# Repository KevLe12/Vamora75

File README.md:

# Vamora75

**An 82-key 75 % mechanical keyboard with a 6° typing angle, a tab-gasket mount, hot-swap sockets
and an on-board RP2040.** Designed by **Kevin Le, Sammy DeGraaff and Mohammed-Mehdi Hamdaoui**.

> **Status: revision 1.7, prototype design checked in software, not built yet.** ERC, DRC, schematic
> parity, plate DRC, CAD interference checks and 34 firmware tests all pass
> ([validation/STATUS.md](validation/STATUS.md)). Build one prototype before a group order and work
> through the open items in [DESIGN_REVIEW.md](DESIGN_REVIEW.md).

Revision 1.4 adopts all 82 key positions and widths from the supplied Custom layout,
including the closer F-row, inward navigation column and End in the top row.
Revision 1.5 moves the controller beside the rear-left USB-C connector and uses four layers.
The short USB pair targets 90 ohms on JLCPCB's JLC04161H-7628 stackup, with a dedicated
In2.Cu ground plane. Order controlled impedance and request the supplier's coupon report;
see [fabrication notes](Manufacturing/FABRICATION.md). Key positions and case geometry are unchanged.

Revision 1.6 incorporates the friend/professor review: USB enters the ESD device on
pins 1/3 and exits on pins 6/4, without PCB copper bypasses. C8 adds a correctly
specified 100 nF 0402 VBUS bypass capacitor. USB track junctions now meet on their
centrelines or at pad/via centres, and termination via drills clear the resistor pads.
The PCB order specifies **black solder mask**, white silkscreen and ENIG.
See [feedback resolution](validation/FEEDBACK_RESOLUTION.md).

Revision 1.7 centres the remaining trace-to-via connections and enables that DRC check.
It adds component-to-component CAD checks, fixes the QMK metadata and protects
CircuitPython boot recovery when the USB host is suspended. See
[release audit](validation/RELEASE_AUDIT.md). In KiCad 3D Viewer, enable
**Appearance → Use board stackup colors** and refresh to display the black mask.

CNC case revision **D5** uses blind M3 threads and 3 mm BOOT access. Send the
[CNC package](Manufacturing/Case_Drawings/Vamora75_case_CNC_D5_package.zip), including its drawings,
to the machinist. It specifies 6061-T6, as machined and deburred; preview colors are illustrative.
Separate print variants retain heat-set inserts. Validate one machined pair before repeating it.

For **PC-CF on the CORE One L**, use the [print package](Manufacturing/Vamora75_PCCF_print.zip)
and [PC-CF guide](Manufacturing/PCCF_PRINT.md). Four oriented parts fit the bed individually;
the package includes an insert-fit coupon. Material budget: three 800 g spools for three cases,
pending actual slicing and first-case validation.

## Features

- Compact 75 % Windows ANSI layout, 82 keys, matching the full Custom layout
- Hot-swap Kailh sockets for any 3- or 5-pin MX-compatible switch
- PCB-mount screw-in stabilisers on plated, copper-reinforced holes; the plate openings let the
  stabiliser housings pass through
- Tab-gasket sandwich mount: 8 plate tabs, 16 gaskets at 20 % compression, optional flex-cut plate
- 6° typing angle; two-piece case whose top follows the key clusters, so no plate shows between
  them; printed in one piece, in 4 pieces for 250 x 210 mm beds, or CNC
- RP2040 on the board (the Raspberry Pi Pico core circuit), USB-C, ESD protection, fuse, BOOT and
  RESET buttons
- QMK + VIA, or CircuitPython with no compiler
- Black PCB with ENIG gold; "Vamora75" across the PCB front, engraved under the case and in gold on
  the plate (under the top case); *Nam Quốc Sơn Hà* and the designers' names on the PCB back
- Generated from source: one command rebuilds the PCB, plate, case, firmware, manufacturing files,
  3D models and renders, then re-runs every check

## Gallery

| Exploded | Top |
|---|---|
|  |  |
| **Profile** | **Underside** |
|  |  |

**PCB + plate + components** (no case): Joe Scotto's MX switches, the PCB-mount stabilisers, Kailh
sockets and every SMD part ([3D file](Mechanical/Vamora75_PCB_plate.step),
[quick-look .glb](Mechanical/Vamora75_PCB_plate.glb)):

### PCB

| Front ("Vamora75" silkscreen) | Back (*Nam Quốc Sơn Hà*, designers, gold stabiliser rings) |
|---|---|
|  |  |
| **With Joe Scotto's switch models** | **FR4 plate (name in gold ENIG, under the top case)** |
|  |  |

## 3D files

| File | Shows | Open with |
|---|---|---|
| [Mechanical/Vamora75_assembly.step](Mechanical/Vamora75_assembly.step) | The whole keyboard: case, gaskets, foams, plate, PCBA, switches, stabilisers, keycaps | FreeCAD, Fusion 360, Onshape, SolidWorks |
| [Mechanical/Vamora75_PCB_plate.step](Mechanical/Vamora75_PCB_plate.step) | PCB + plate + every component, without the case | any STEP viewer |
| [Mechanical/Vamora75_PCB_plate.glb](Mechanical/Vamora75_PCB_plate.glb) | The same, as a light coloured model | Windows 3D Viewer, Blender, any web glTF viewer |
| [Mechanical/Vamora75_PCBA.step](Mechanical/Vamora75_PCBA.step) | The PCBA only (KiCad export) | any STEP viewer |
| [PCB/Vamora75.kicad_pro](PCB/Vamora75.kicad_pro) | Schematic and board; press Alt+3 for the 3D view | KiCad 10 |

Case parts, the plate and the soft parts are in [Mechanical/](Mechanical) as STEP/STL/DXF.

## Specifications

| | |
|---|---|
| Layout | 82 keys: exploded 75 % Windows ANSI with an F-row in clusters, a Del/Home/PgUp/PgDn/End column, Custom-style arrow positions (0.25u gaps to RShift and RCtrl; 0.25u lower), 1.75u RShift and 6.25u space ([layout](Previews/layout.png)) |
| Switches | Any MX-compatible switch, 3- or 5-pin, in Kailh CPG151101S11 hot-swap sockets (ScottoKicad `Hotswap_MX` footprints) |
| Stabilisers | PCB-mount screw-in: Backspace (2u), Enter and LShift (2.25u), Space (6.25u), standard orientation. Plated holes with 4.6 / 6.0 mm copper reinforcement rings; plate openings 7.0 x 14 mm |
| Controller | RP2040, W25Q16JV 2 MB flash, 12 MHz crystal (the Raspberry Pi Pico core circuit), BOOT and RESET buttons |
| USB | USB-C (HRO TYPE-C-31-M-12), USB 2.0 full speed, 5.1 kΩ CC resistors (C-C and A-C cables), USBLC6-2SC6 ESD protection, 0.5 A PTC fuse, XC6206 3.3 V LDO |
| Matrix | 6 x 16, COL2ROW, one 1N4148W per key |
| PCB | 315.56 x 129.83 mm, 4 layers, 1.6 mm nominal, black solder mask, white silkscreen, ENIG. All SMT parts on the bottom (one-sided assembly), dedicated In2.Cu GND plane plus outer ground pours |
| Plate | FR4, 1.5 mm (1.6 mm also fits), black, 8 gasket tabs, optional flex cuts, "Vamora75" in gold ENIG |
| Mount | Tab-gasket sandwich: 16 gaskets of 20 x 4.5 x 2 mm at 20 % compression. PCB and plate float as one unit |
| Case | Two pieces, 6° typing angle, 20.98 mm high at the front and 37.06 mm at the rear, 339.56 x 156.73 mm. CNC D5: 8 M3 screws into blind M3 x 0.5 threads. Separate print variants use heat-set inserts. "Vamora75" engraved underneath |
| Firmware | QMK + VIA, or CircuitPython |

## Bill of materials

<!-- BOM:start (generated by Source/export_manufacturing.py) -->
Full list: [BOM.csv](BOM.csv). The PCBA parts are placed by JLCPCB from
[Vamora75_BOM_JLCPCB.csv](Manufacturing/PCB/Vamora75_BOM_JLCPCB.csv) and
[Vamora75_CPL_JLCPCB.csv](Manufacturing/PCB/Vamora75_CPL_JLCPCB.csv); you only buy the kit items.

**Kit: what to buy or make**

| Item | Qty | Specification | Source / file |
|---|---|---|---|
| PCBA (this design) | 1 | 4-layer JLC04161H-7628 1.6 mm nominal, black mask, ENIG, bottom SMT, USB 90 ohm +/-10% | Manufacturing/PCB - JLCPCB |
| FR4 plate | 1 | 1.5 mm (1.6 mm fits), black mask, ENIG for the gold name | Manufacturing/Plate - any PCB fab |
| Case top | 1 | CNC D5 6061-T6; separate PETG/ASA print variant | Mechanical/Case (CNC); print_one_piece or print_split (print) |
| Case bottom | 1 | CNC D5 6061-T6 solid wedge, 6 deg; separate print variant | Mechanical/Case (CNC); print_one_piece or print_split (print) |
| MX-compatible switches | 82 | 3-pin or 5-pin | user choice |
| Keycaps | 82 | 1u x 71, 1.25u x 3, 1.5u x 2, 1.75u x 2, 2u x 1, 2.25u x 2, 6.25u x 1 | any MX set with a 75 % kit (1.75u RShift, 6.25u space) |
| PCB-mount screw-in stabilisers | 4 | 3 x 2u (Backspace, Enter, LShift) + 1 x 6.25u (Space) | Durock/Cherry/TX |
| Gaskets | 16 | 20 x 4.5 x 2 mm Poron 4701-50 or 40A silicone | Mechanical/Soft DXF |
| Case foam | 1 | 3 mm PE / Poron | Mechanical/Soft DXF |
| Plate foam (optional) | 1 | 3.5 mm Poron / PE, with stabiliser/wire windows | Mechanical/Soft DXF |
| Screws | 8 | M3 x 8 ISO 4762 socket head |  |
| Heat-set inserts (print only) | 8 | M3 x 4 x 4.0 mm heat-set insert (not used in CNC case) | Mechanical/Case/print_one_piece or print_split |
| Dowel pins (split print only) | 5 | 3 x 12 mm steel dowel (or printed pin) | only for the 4-piece printed case |
| Bumpers | 4 | 10 x 3 mm silicone bumper |  |
| USB-C cable | 1 | overmould <= 12.3 x 6.5 mm |  |

**PCBA: parts on the board** (198 placements, all on the bottom side)

| Part | Qty | Designators | Footprint | LCSC |
|---|---|---|---|---|
| 10uF CL10A106KP8NNNC | 2 | C1-C2 | C_0603_1608Metric | [C19702](https://www.lcsc.com/product-detail/C19702.html) |
| 100nF CL05B104KO5NNNC | 11 | C3-C12, C15 | Capacitor_0402 | [C1525](https://www.lcsc.com/product-detail/C1525.html) |
| 1uF CL05A105KA5NQNC | 2 | C13-C14 | Capacitor_0402 | [C52923](https://www.lcsc.com/product-detail/C52923.html) |
| 15pF 0402CG150J500NT | 2 | C16-C17 | Capacitor_0402 | [C1548](https://www.lcsc.com/product-detail/C1548.html) |
| 1N4148W | 82 | D1-D82 | Diode_SOD-123 | [C81598](https://www.lcsc.com/product-detail/C81598.html) |
| 500mA SMD0805-050 | 1 | F1 | Fuse_0805_2012Metric | [C66452](https://www.lcsc.com/product-detail/C66452.html) |
| HRO TYPE-C-31-M-12 | 1 | J1 | USB_C_HRO_TYPE-C-31-M-12 | [C165948](https://www.lcsc.com/product-detail/C165948.html) |
| 5.1k 0402WGF5101TCE | 2 | R1-R2 | Resistor_0402 | [C25905](https://www.lcsc.com/product-detail/C25905.html) |
| 27R 0402WGF270JTCE | 2 | R3-R4 | Resistor_0402 | [C25100](https://www.lcsc.com/product-detail/C25100.html) |
| 10k 0402WGF1002TCE | 2 | R5, R7 | Resistor_0402 | [C25744](https://www.lcsc.com/product-detail/C25744.html) |
| 1k 0402WGF1001TCE | 2 | R6, R8 | Resistor_0402 | [C11702](https://www.lcsc.com/product-detail/C11702.html) |
| Kailh CPG151101S11 MX hot-swap socket | 82 | SW1-SW82 | Kailh_CPG151101S11 | [C5156480](https://www.lcsc.com/product-detail/C5156480.html) |
| BOOT TS-1187A-B-A-B | 1 | SW90 | SW_Push_1P1T_XKB_TS-1187A | [C318884](https://www.lcsc.com/product-detail/C318884.html) |
| RESET TS-1187A-B-A-B | 1 | SW91 | SW_Push_1P1T_XKB_TS-1187A | [C318884](https://www.lcsc.com/product-detail/C318884.html) |
| RP2040 | 1 | U1 | QFN-56-1EP_7x7mm_P0.4mm_EP3.2x3.2mm_ThermalVias | [C2040](https://www.lcsc.com/product-detail/C2040.html) |
| USBLC6-2SC6 | 1 | U2 | ESD_SOT-23-6 | [C7519](https://www.lcsc.com/product-detail/C7519.html) |
| XC6206P332MR | 1 | U3 | Voltage_SOT-23 | [C5446](https://www.lcsc.com/product-detail/C5446.html) |
| W25Q16JVUXIQ | 1 | U4 | Winbond_USON-8-1EP_3x2mm_P0.5mm_EP0.2x1.6mm | [C2843335](https://www.lcsc.com/product-detail/C2843335.html) |
| 12MHz ABM8-272-T3 | 1 | Y1 | Crystal_SMD_3225-4Pin_3.2x2.5mm | [C20625731](https://www.lcsc.com/product-detail/C20625731.html) |
<!-- BOM:end -->

## Getting started

1. Read [DESIGN_REVIEW.md](DESIGN_REVIEW.md): the mount, the stabilisers, what changed, and what to
   check on the first prototype.
2. Order the PCBA, the plate, the case and the soft parts:
   [Manufacturing/FABRICATION.md](Manufacturing/FABRICATION.md).
3. Assemble it: [BUILD_GUIDE.md](BUILD_GUIDE.md).
4. Flash the firmware: [Firmware/README.md](Firmware/README.md).
5. To change the design, edit the parameter files and rebuild: [Source/README.md](Source/README.md).

## Repository

| Folder | Contents |
|---|---|
| [PCB/](PCB) | KiCad 10 project: schematic, 4-layer board, project footprint library (ScottoKicad + KiCad stock) with 3D models, custom DRC rules |
| [Plate/](Plate) | KiCad boards for ordering the FR4 plate as a PCB (standard and flex-cut) |
| [Mechanical/](Mechanical) | Case (one-piece and 4-piece print split), plate DXF/STEP/STL, gasket and foam DXFs, assembly STEP, PCB + plate STEP/GLB, PCBA STEP, key positions |
| [Manufacturing/](Manufacturing) | JLCPCB-ready Gerbers/drill, BOM + CPL, schematic PDF, assembly drawing, plate Gerbers, kit BOM |
| [Firmware/](Firmware) | QMK + VIA source, VIA definition, CircuitPython, KLE layout |
| [Artwork/](Artwork) | The "Vamora75" name in SVG/PNG/DXF ([NAME.md](Artwork/NAME.md)) |
| [Previews/](Previews) | Renders |
| [Source/](Source) | Python generators for everything (`build_all.py`) |
| [validation/](validation) | ERC/DRC, mechanical, plate and firmware reports |
| [Licenses/](Licenses) | Third-party licenses and notices; see [ATTRIBUTION.md](ATTRIBUTION.md) |
| [Reference/](Reference) | Input snapshots (Keyboard75, Aster75) |

## Revisions

- **1.7** (2026-11-12): centred via joins, firmware recovery fixes, component and print-fastener checks; rebuilt release.
- **1.6** (2026-11-12): ESD flow-through routing, C8 VBUS bypass, robust USB junctions, regression checks and revision-organized delivery.
- **1.5** (2026-11-11): short USB routing, nearby controller, four-layer JLCPCB controlled-impedance stackup, refreshed outputs and PC-CF print package.
- **1.4** (2026-11-03): full Custom layout, narrower PCB and case, controller under
  the spacebar, rear-left USB-C, revised routing, plate, foam, firmware and drawings.
- **1.3** (2026-10-31): USB-C moved to the rear-left corner; only the four arrow keys
  moved to match the Custom layout relative to Right Shift. Updated PCB, case,
  plate, firmware layout, manufacturing drawings and validation outputs.
- **1.2** (2026-10-03): top case covers the gaps between key clusters, plate openings and foam
  windows for PCB-mount stabilisers, plated and reinforced stabiliser holes, black PCB, designers'
  names on the PCB back, sculpted keycaps, new 3D files and renders.
- **1.1**: arrow cluster moved away from the nav column, Joe Scotto's ScottoKicad footprints and
  models, name-only branding.
- **1.0**: on-board RP2040, new matrix and routing, 6° gasket-mount case.

Details: [CHANGELOG.md](CHANGELOG.md).

## Credits

Designed by **Kevin Le, Sammy DeGraaff and Mohammed-Mehdi Hamdaoui** (team Vamora).

Footprints and 3D models for the switches, sockets, stabilisers and several components are from
Joe Scotto's [ScottoKicad](https://github.com/joe-scotto/scottokeebs). Third-party data and licences:
[ATTRIBUTION.md](ATTRIBUTION.md) and [Licenses/](Licenses).

Local archives and build intermediates are omitted from the GitHub snapshot. No project-wide
license has been selected for the team's original work.

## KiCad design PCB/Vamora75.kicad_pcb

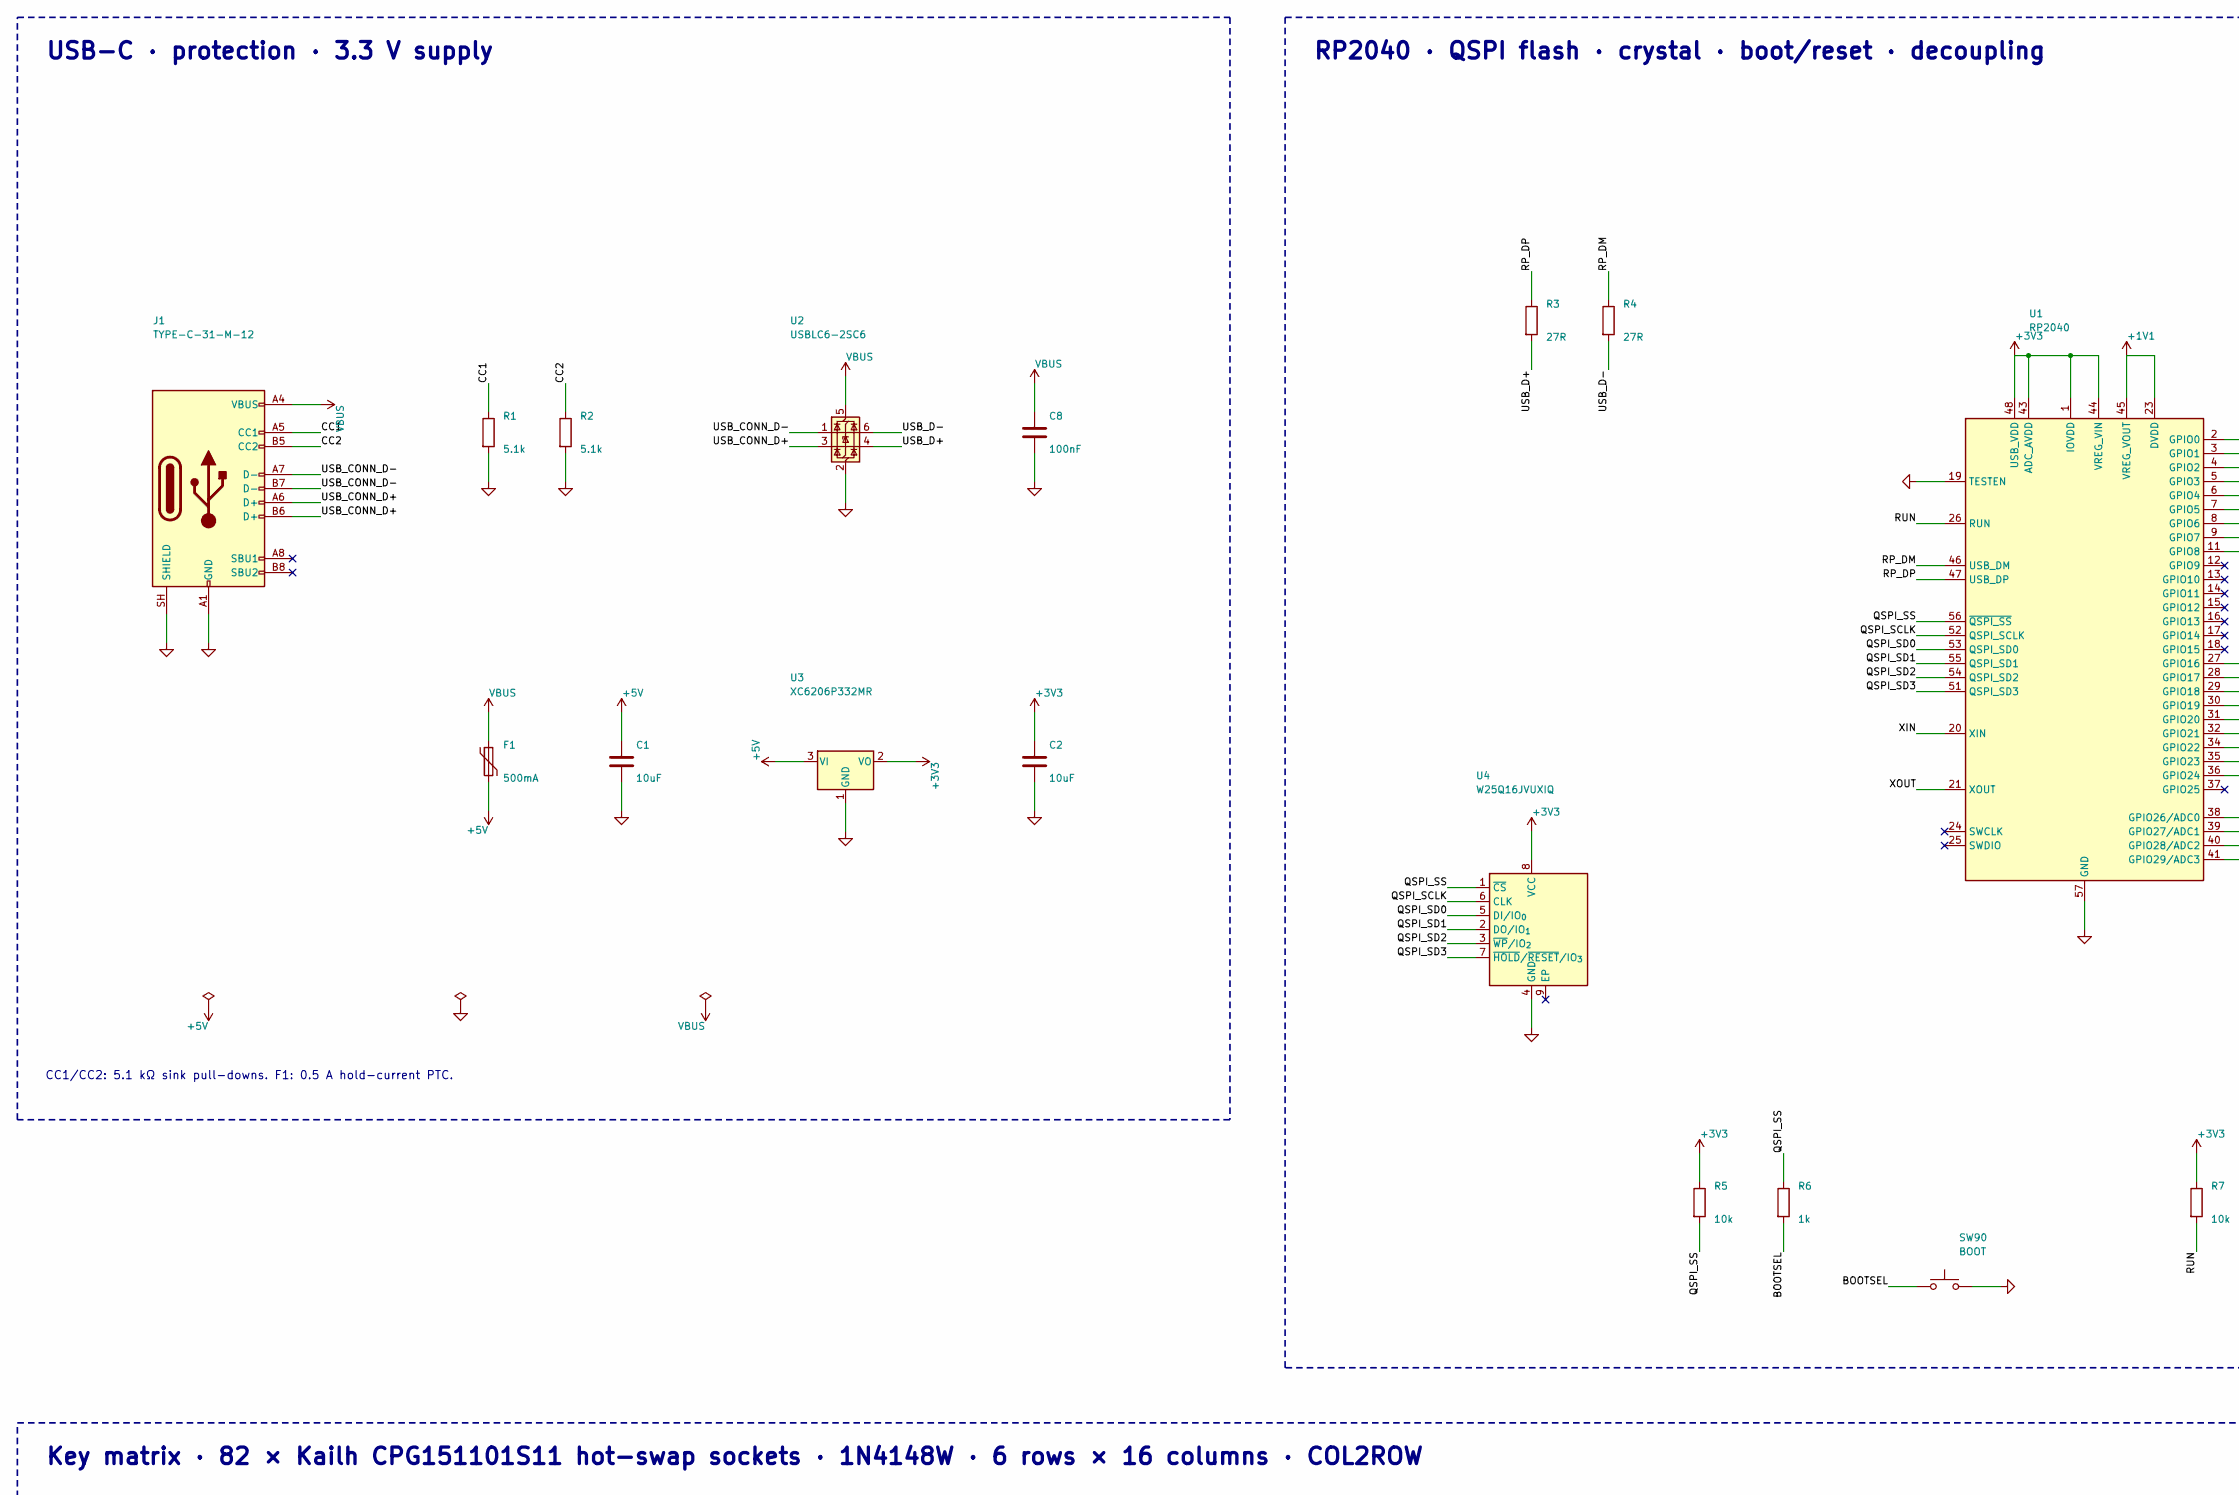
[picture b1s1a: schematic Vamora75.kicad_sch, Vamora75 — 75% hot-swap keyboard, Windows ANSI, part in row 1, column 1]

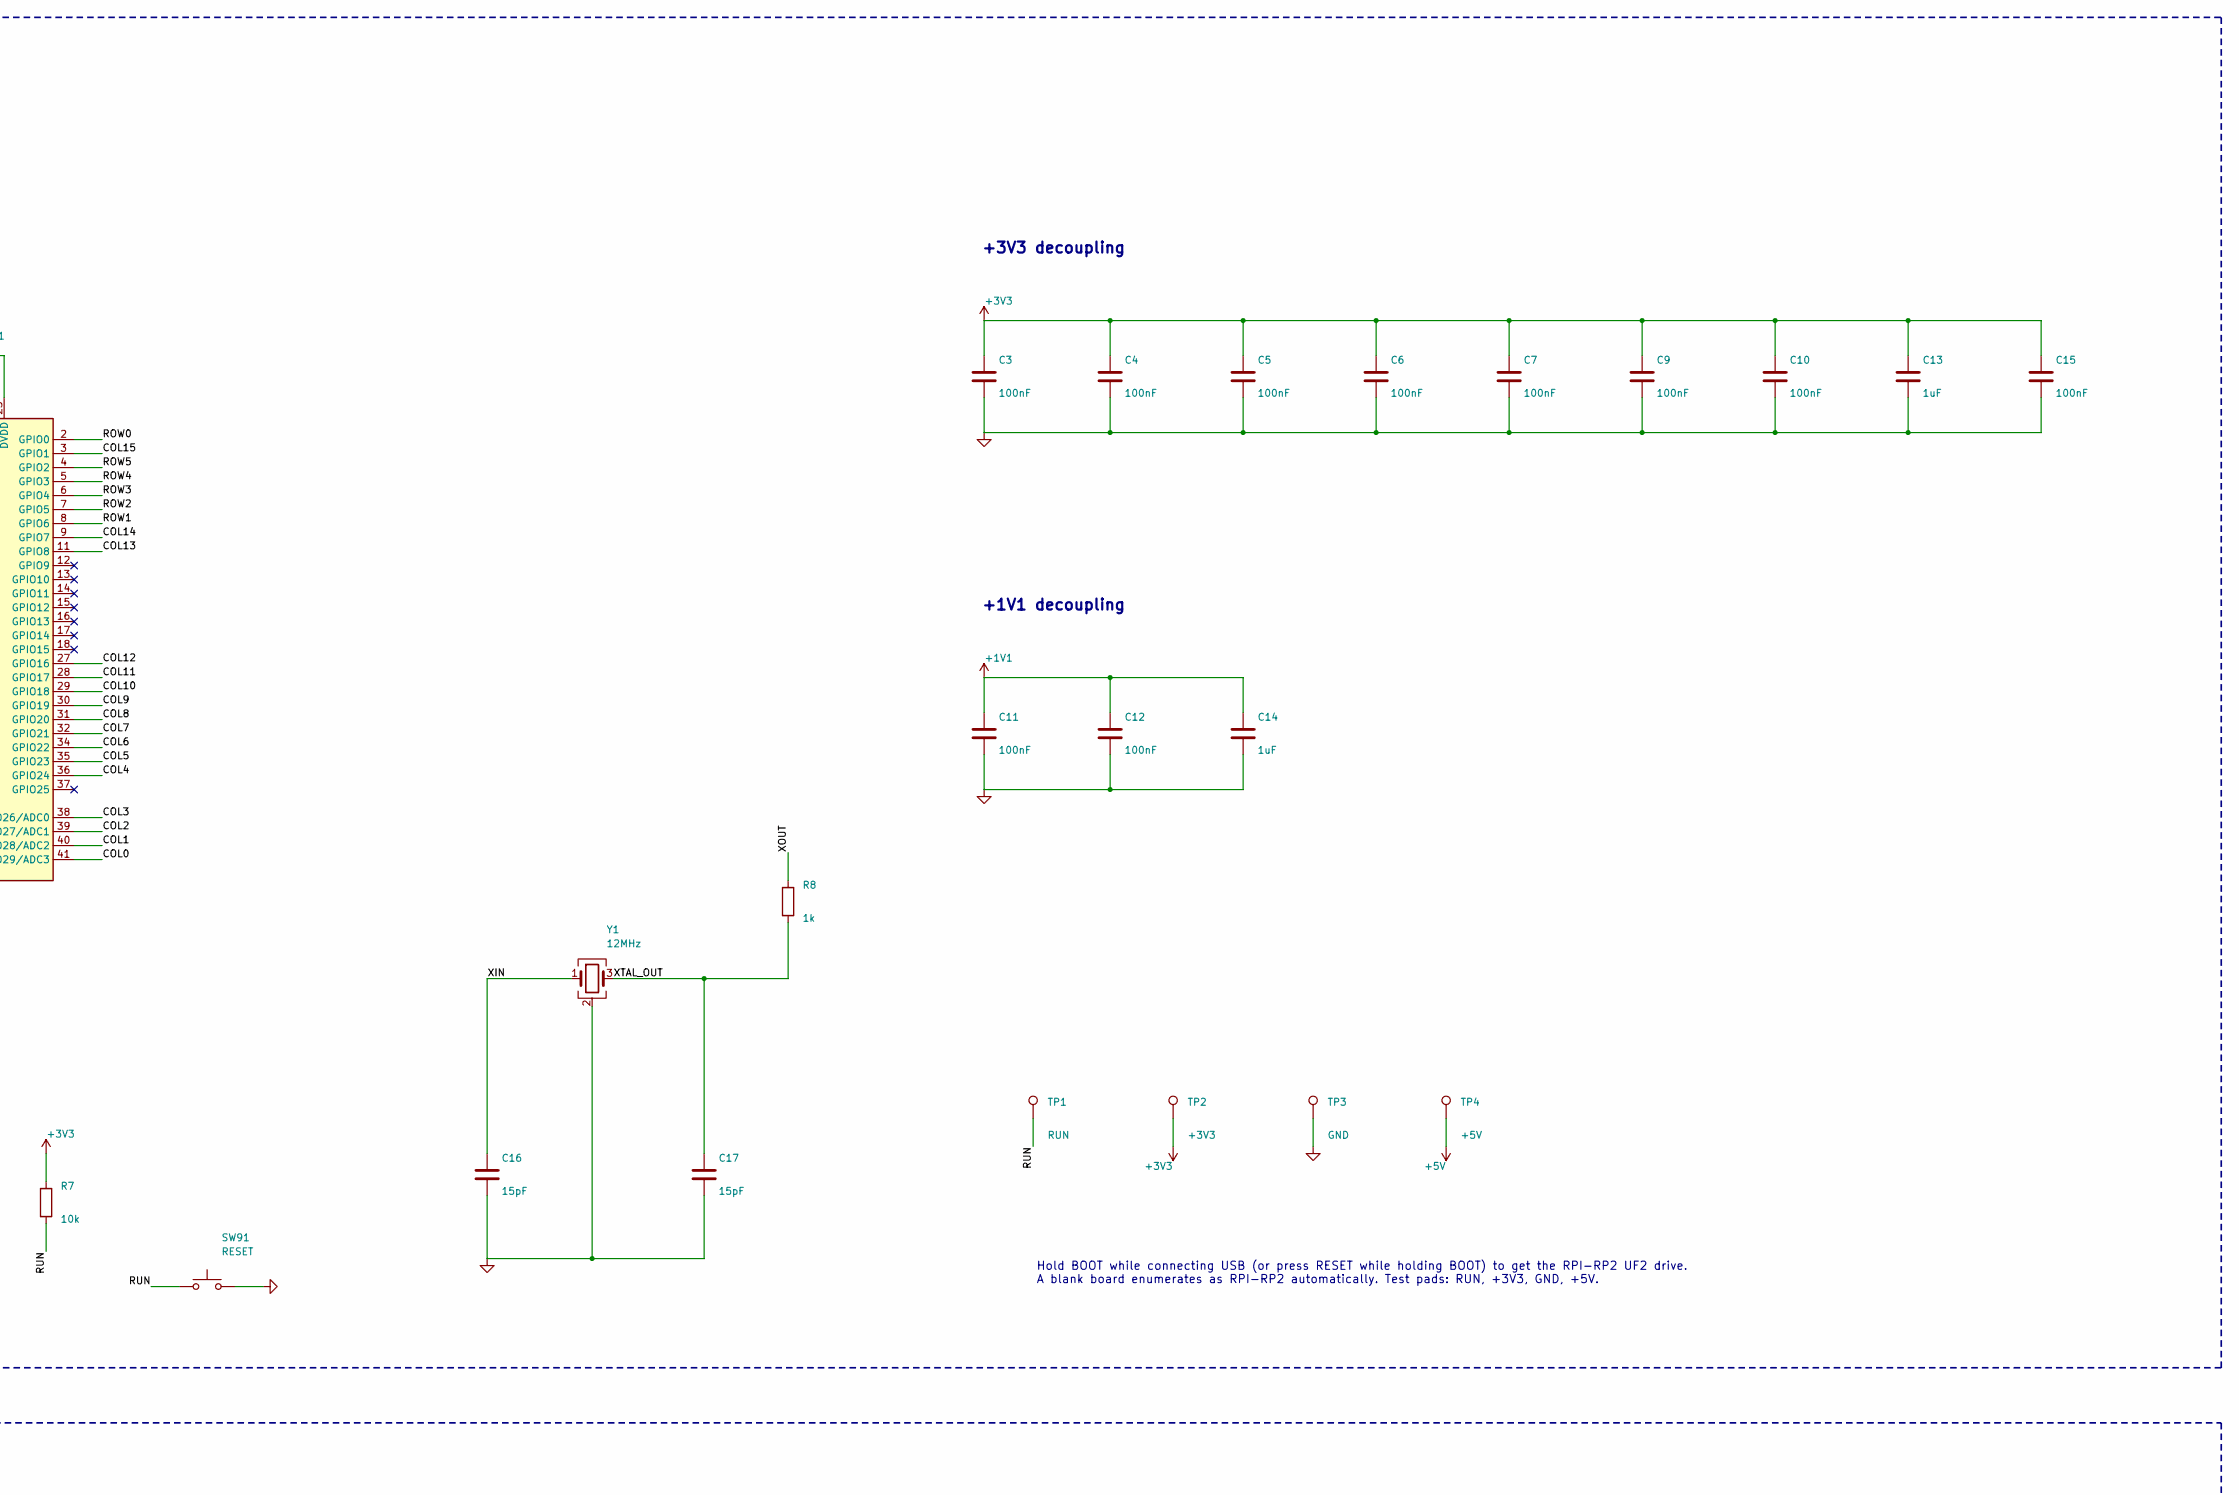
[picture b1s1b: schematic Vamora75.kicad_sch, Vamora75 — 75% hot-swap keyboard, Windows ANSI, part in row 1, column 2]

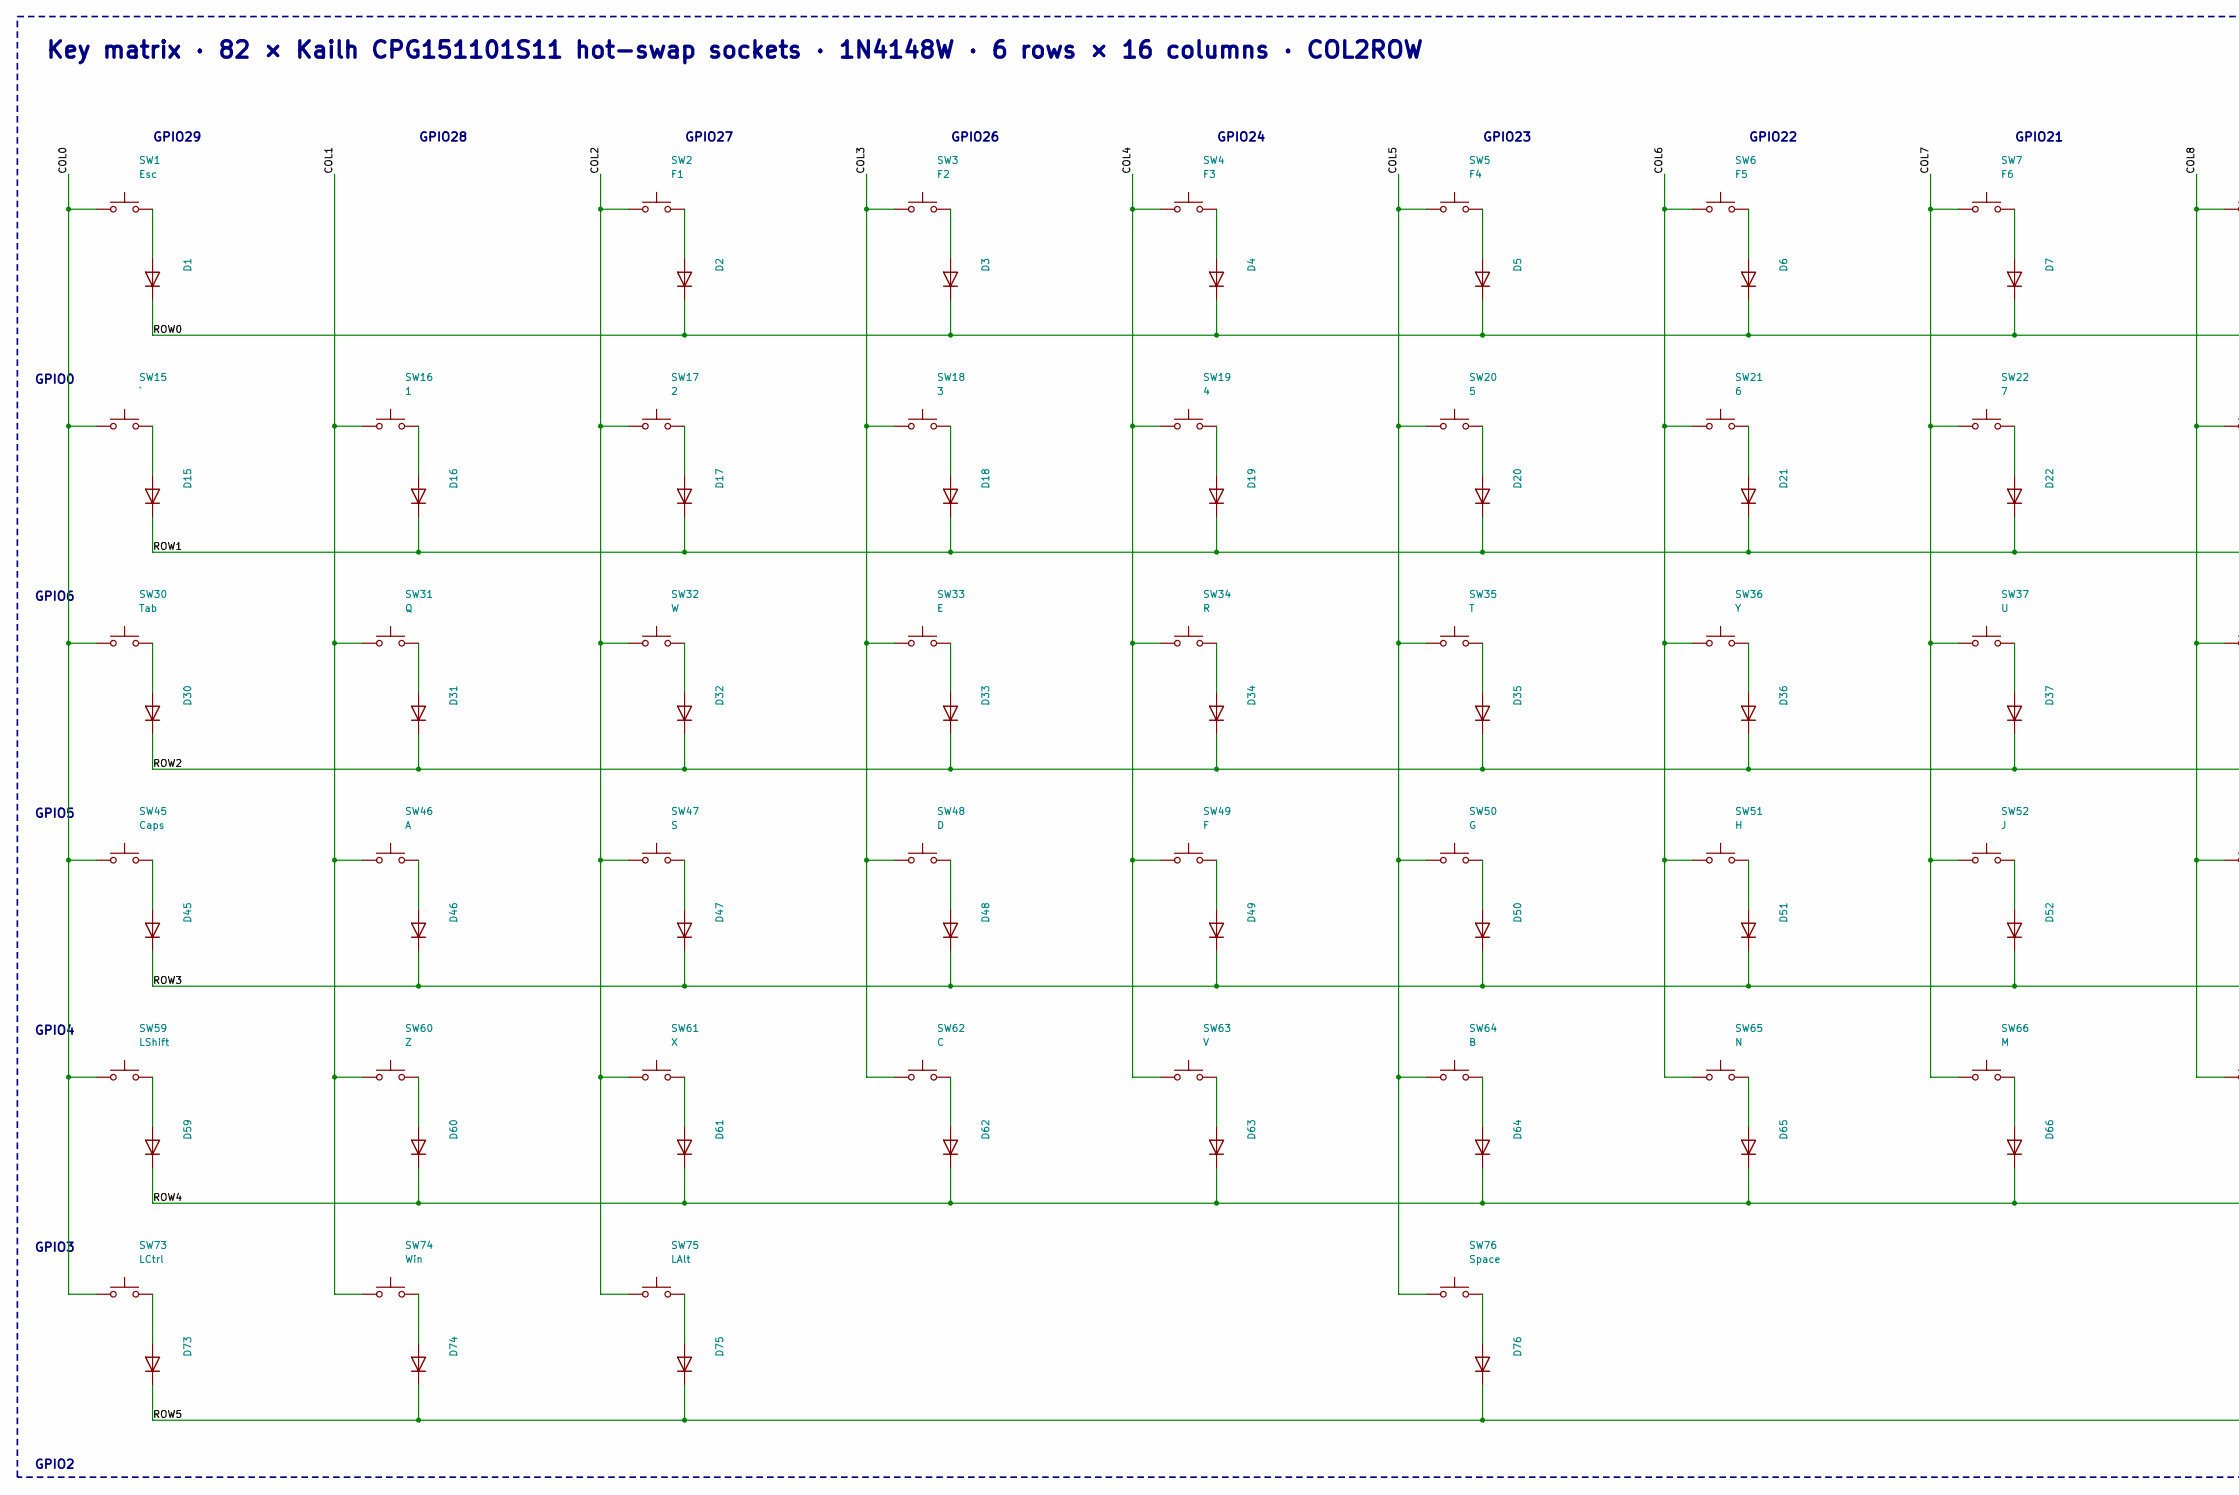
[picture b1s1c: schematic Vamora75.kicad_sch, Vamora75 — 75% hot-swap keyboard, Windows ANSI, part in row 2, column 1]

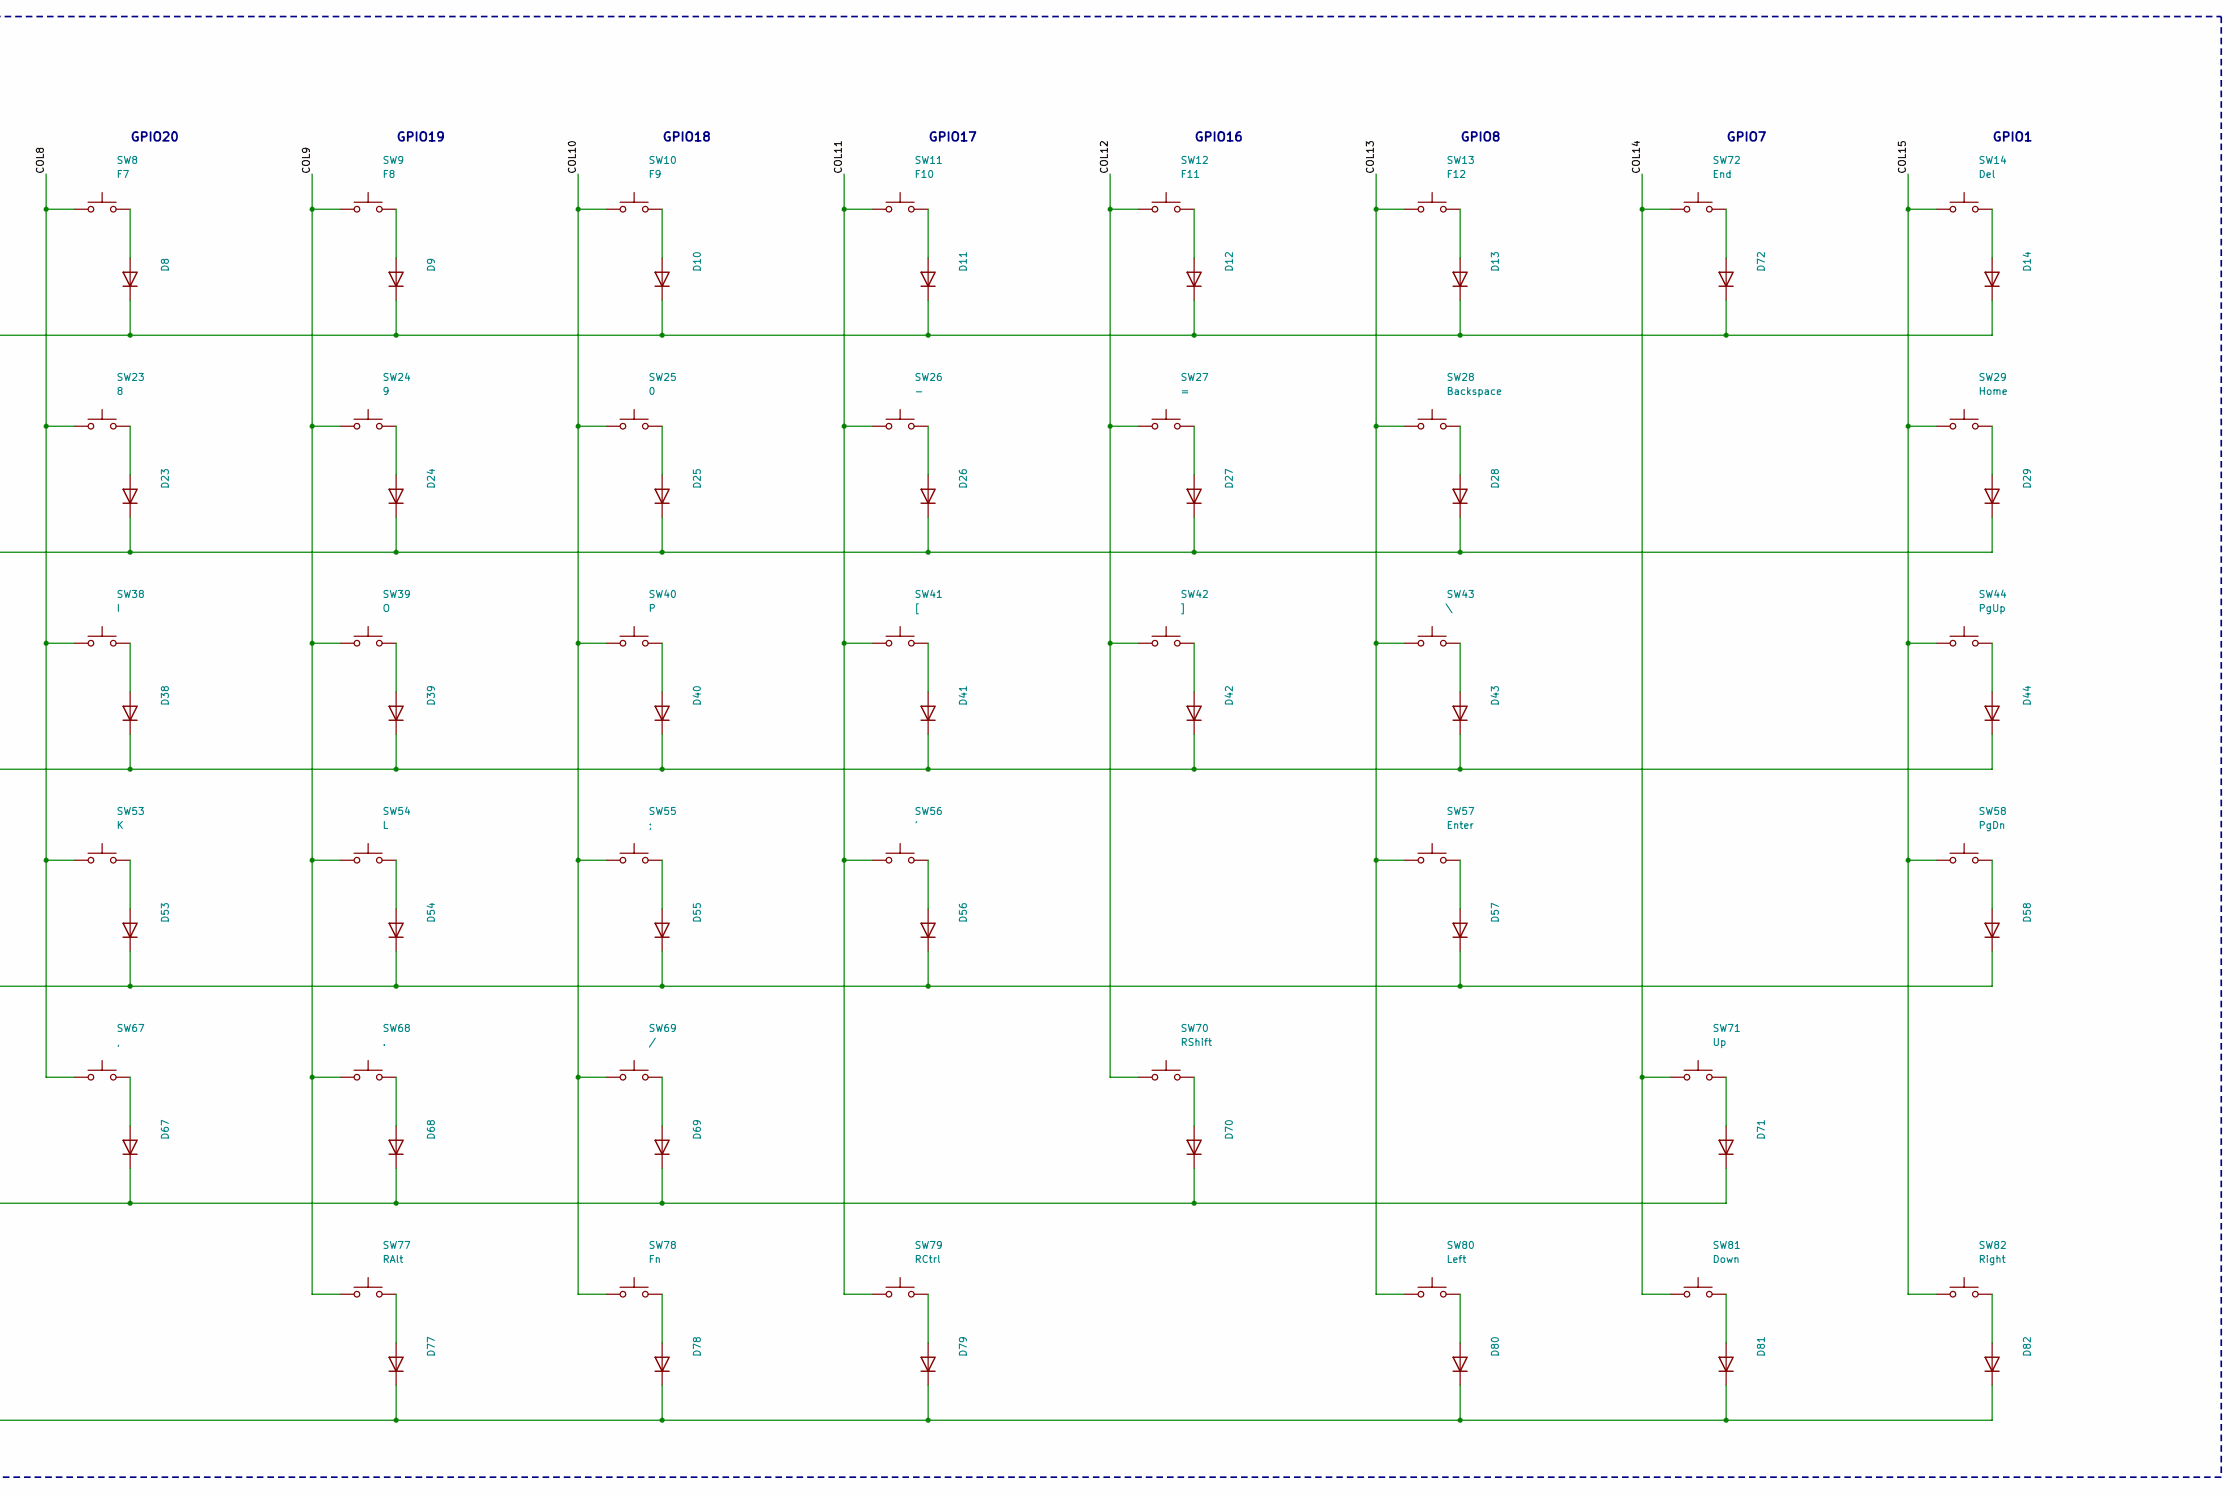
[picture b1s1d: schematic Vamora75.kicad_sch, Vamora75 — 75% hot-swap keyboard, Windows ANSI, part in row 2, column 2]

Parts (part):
C1, C2: 10uF; C_0603_1608Metric; MPN CL10A106KP8NNNC; LCSC C19702
C3, C4, C5, C6, C7, C8, C9, C10, C11, C12, C15: 100nF; Capacitor_0402; MPN CL05B104KO5NNNC; LCSC C1525
C13, C14: 1uF; Capacitor_0402; MPN CL05A105KA5NQNC; LCSC C52923
C16, C17: 15pF; Capacitor_0402; MPN 0402CG150J500NT; LCSC C1548
D1, D2, D3, D4, D5, D6, D7, D8, D9, D10, D11, D12, D13, D14, D15, D16, D17, D18, D19, D20, D21, D22, D23, D24, D25, D26, D27, D28, D29, D30, D31, D32, D33, D34, D35, D36, D37, D38, D39, D40, D41, D42, D43, D44, D45, D46, D47, D48, D49, D50, D51, D52, D53, D54, D55, D56, D57, D58, D59, D60, D61, D62, D63, D64, D65, D66, D67, D68, D69, D70, D71, D72, D73, D74, D75, D76, D77, D78, D79, D80, D81, D82: 1N4148W; Diode_SOD-123; MPN 1N4148W; LCSC C81598
F1: 500mA; Fuse_0805_2012Metric; MPN SMD0805-050; LCSC C66452
J1: TYPE-C-31-M-12; USB_C_HRO_TYPE-C-31-M-12; MPN HRO TYPE-C-31-M-12; LCSC C165948
R1, R2: 5.1k; Resistor_0402; MPN 0402WGF5101TCE; LCSC C25905
R3, R4: 27R; Resistor_0402; MPN 0402WGF270JTCE; LCSC C25100
R5, R7: 10k; Resistor_0402; MPN 0402WGF1002TCE; LCSC C25744
R6, R8: 1k; Resistor_0402; MPN 0402WGF1001TCE; LCSC C11702
SW1: Esc; Hotswap_MX_1.00u; MPN Kailh CPG151101S11; LCSC C5156480
SW2: F1; Hotswap_MX_1.00u_USB; MPN Kailh CPG151101S11; LCSC C5156480
SW3: F2; Hotswap_MX_1.00u; MPN Kailh CPG151101S11; LCSC C5156480
SW4: F3; Hotswap_MX_1.00u; MPN Kailh CPG151101S11; LCSC C5156480
SW5: F4; Hotswap_MX_1.00u; MPN Kailh CPG151101S11; LCSC C5156480
SW6: F5; Hotswap_MX_1.00u; MPN Kailh CPG151101S11; LCSC C5156480
SW7: F6; Hotswap_MX_1.00u; MPN Kailh CPG151101S11; LCSC C5156480
SW8: F7; Hotswap_MX_1.00u; MPN Kailh CPG151101S11; LCSC C5156480
SW9: F8; Hotswap_MX_1.00u; MPN Kailh CPG151101S11; LCSC C5156480
SW10: F9; Hotswap_MX_1.00u; MPN Kailh CPG151101S11; LCSC C5156480
SW11: F10; Hotswap_MX_1.00u; MPN Kailh CPG151101S11; LCSC C5156480
SW12: F11; Hotswap_MX_1.00u; MPN Kailh CPG151101S11; LCSC C5156480
SW13: F12; Hotswap_MX_1.00u; MPN Kailh CPG151101S11; LCSC C5156480
SW14: Del; Hotswap_MX_1.00u; MPN Kailh CPG151101S11; LCSC C5156480
SW15: `; Hotswap_MX_1.00u; MPN Kailh CPG151101S11; LCSC C5156480
SW16: 1; Hotswap_MX_1.00u; MPN Kailh CPG151101S11; LCSC C5156480
SW17: 2; Hotswap_MX_1.00u; MPN Kailh CPG151101S11; LCSC C5156480
SW18: 3; Hotswap_MX_1.00u; MPN Kailh CPG151101S11; LCSC C5156480
SW19: 4; Hotswap_MX_1.00u; MPN Kailh CPG151101S11; LCSC C5156480
SW20: 5; Hotswap_MX_1.00u; MPN Kailh CPG151101S11; LCSC C5156480
SW21: 6; Hotswap_MX_1.00u; MPN Kailh CPG151101S11; LCSC C5156480
SW22: 7; Hotswap_MX_1.00u; MPN Kailh CPG151101S11; LCSC C5156480
SW23: 8; Hotswap_MX_1.00u; MPN Kailh CPG151101S11; LCSC C5156480
SW24: 9; Hotswap_MX_1.00u; MPN Kailh CPG151101S11; LCSC C5156480
SW25: 0; Hotswap_MX_1.00u; MPN Kailh CPG151101S11; LCSC C5156480
SW26: -; Hotswap_MX_1.00u; MPN Kailh CPG151101S11; LCSC C5156480
SW27: =; Hotswap_MX_1.00u; MPN Kailh CPG151101S11; LCSC C5156480
SW28: Backspace; Hotswap_MX_2.00u; MPN Kailh CPG151101S11; LCSC C5156480
SW29: Home; Hotswap_MX_1.00u; MPN Kailh CPG151101S11; LCSC C5156480
SW30: Tab; Hotswap_MX_1.50u; MPN Kailh CPG151101S11; LCSC C5156480
SW31: Q; Hotswap_MX_1.00u; MPN Kailh CPG151101S11; LCSC C5156480
SW32: W; Hotswap_MX_1.00u; MPN Kailh CPG151101S11; LCSC C5156480
SW33: E; Hotswap_MX_1.00u; MPN Kailh CPG151101S11; LCSC C5156480
SW34: R; Hotswap_MX_1.00u; MPN Kailh CPG151101S11; LCSC C5156480
SW35: T; Hotswap_MX_1.00u; MPN Kailh CPG151101S11; LCSC C5156480
SW36: Y; Hotswap_MX_1.00u; MPN Kailh CPG151101S11; LCSC C5156480
SW37: U; Hotswap_MX_1.00u; MPN Kailh CPG151101S11; LCSC C5156480
SW38: I; Hotswap_MX_1.00u; MPN Kailh CPG151101S11; LCSC C5156480
SW39: O; Hotswap_MX_1.00u; MPN Kailh CPG151101S11; LCSC C5156480
SW40: P; Hotswap_MX_1.00u; MPN Kailh CPG151101S11; LCSC C5156480
SW41: [; Hotswap_MX_1.00u; MPN Kailh CPG151101S11; LCSC C5156480
SW42: ]; Hotswap_MX_1.00u; MPN Kailh CPG151101S11; LCSC C5156480
SW43: \; Hotswap_MX_1.50u; MPN Kailh CPG151101S11; LCSC C5156480
SW44: PgUp; Hotswap_MX_1.00u; MPN Kailh CPG151101S11; LCSC C5156480
SW45: Caps; Hotswap_MX_1.75u; MPN Kailh CPG151101S11; LCSC C5156480
SW46: A; Hotswap_MX_1.00u; MPN Kailh CPG151101S11; LCSC C5156480
SW47: S; Hotswap_MX_1.00u; MPN Kailh CPG151101S11; LCSC C5156480
SW48: D; Hotswap_MX_1.00u; MPN Kailh CPG151101S11; LCSC C5156480
SW49: F; Hotswap_MX_1.00u; MPN Kailh CPG151101S11; LCSC C5156480
SW50: G; Hotswap_MX_1.00u; MPN Kailh CPG151101S11; LCSC C5156480
SW51: H; Hotswap_MX_1.00u; MPN Kailh CPG151101S11; LCSC C5156480
SW52: J; Hotswap_MX_1.00u; MPN Kailh CPG151101S11; LCSC C5156480
SW53: K; Hotswap_MX_1.00u; MPN Kailh CPG151101S11; LCSC C5156480
SW54: L; Hotswap_MX_1.00u; MPN Kailh CPG151101S11; LCSC C5156480
SW55: ;; Hotswap_MX_1.00u; MPN Kailh CPG151101S11; LCSC C5156480
SW56: '; Hotswap_MX_1.00u; MPN Kailh CPG151101S11; LCSC C5156480
SW57: Enter; Hotswap_MX_2.25u; MPN Kailh CPG151101S11; LCSC C5156480
SW58: PgDn; Hotswap_MX_1.00u; MPN Kailh CPG151101S11; LCSC C5156480
SW59: LShift; Hotswap_MX_2.25u; MPN Kailh CPG151101S11; LCSC C5156480
SW60: Z; Hotswap_MX_1.00u; MPN Kailh CPG151101S11; LCSC C5156480
SW61: X; Hotswap_MX_1.00u; MPN Kailh CPG151101S11; LCSC C5156480
SW62: C; Hotswap_MX_1.00u; MPN Kailh CPG151101S11; LCSC C5156480
SW63: V; Hotswap_MX_1.00u; MPN Kailh CPG151101S11; LCSC C5156480
SW64: B; Hotswap_MX_1.00u; MPN Kailh CPG151101S11; LCSC C5156480
SW65: N; Hotswap_MX_1.00u; MPN Kailh CPG151101S11; LCSC C5156480
SW66: M; Hotswap_MX_1.00u; MPN Kailh CPG151101S11; LCSC C5156480
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
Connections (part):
+1V1: C11.1, C12.1, C14.1, U1.23 (DVDD), U1.45 (VREG_VOUT), U1.50 (DVDD)
+3V3: C2.1, C3.1, C4.1, C5.1, C6.1, C7.1, C9.1, C10.1, C13.1, C15.1, R5.1, R7.1, TP2.1, U1.1 (IOVDD), U1.10 (IOVDD), U1.22 (IOVDD), U1.33 (IOVDD), U1.42 (IOVDD), U1.43 (ADC_AVDD), U1.44 (VREG_VIN), U1.48 (USB_VDD), U1.49 (IOVDD), U3.2 (VO), U4.8 (VCC)
+5V: C1.1, F1.2, TP4.1, U3.3 (VI)
/BOOTSEL: R6.2, SW90.1
/CC1: J1.A5 (CC1), R1.1
/CC2: J1.B5 (CC2), R2.1
/COL0: SW1.1, SW15.1, SW30.1, SW45.1, SW59.1, SW73.1, U1.41 (GPIO29/ADC3)
/COL1: SW16.1, SW31.1, SW46.1, SW60.1, SW74.1, U1.40 (GPIO28/ADC2)
/COL2: SW2.1, SW17.1, SW32.1, SW47.1, SW61.1, SW75.1, U1.39 (GPIO27/ADC1)
/COL3: SW3.1, SW18.1, SW33.1, SW48.1, SW62.1, U1.38 (GPIO26/ADC0)
/COL4: SW4.1, SW19.1, SW34.1, SW49.1, SW63.1, U1.36 (GPIO24)
/COL5: SW5.1, SW20.1, SW35.1, SW50.1, SW64.1, SW76.1, U1.35 (GPIO23)
/COL6: SW6.1, SW21.1, SW36.1, SW51.1, SW65.1, U1.34 (GPIO22)
/COL7: SW7.1, SW22.1, SW37.1, SW52.1, SW66.1, U1.32 (GPIO21)
/COL8: SW8.1, SW23.1, SW38.1, SW53.1, SW67.1, U1.31 (GPIO20)
/COL9: SW9.1, SW24.1, SW39.1, SW54.1, SW68.1, SW77.1, U1.30 (GPIO19)
/COL10: SW10.1, SW25.1, SW40.1, SW55.1, SW69.1, SW78.1, U1.29 (GPIO18)
/COL11: SW11.1, SW26.1, SW41.1, SW56.1, SW79.1, U1.28 (GPIO17)
/COL12: SW12.1, SW27.1, SW42.1, SW70.1, U1.27 (GPIO16)
/COL13: SW13.1, SW28.1, SW43.1, SW57.1, SW80.1, U1.11 (GPIO8)
/COL14: SW71.1, SW72.1, SW81.1, U1.9 (GPIO7)
/COL15: SW14.1, SW29.1, SW44.1, SW58.1, SW82.1, U1.3 (GPIO1)
/QSPI_SCLK: U1.52 (QSPI_SCLK), U4.6 (CLK)
/QSPI_SD0: U1.53 (QSPI_SD0), U4.5 (DI/IO_{0})
/QSPI_SD1: U1.55 (QSPI_SD1), U4.2 (DO/IO_{1})
/QSPI_SD2: U1.54 (QSPI_SD2), U4.3 (~WP/IO_{2})
/QSPI_SD3: U1.51 (QSPI_SD3), U4.7 (~HOLD/~RESET/IO_{3})
/QSPI_SS: R5.2, R6.1, U1.56 (~QSPI_SS), U4.1 (~CS)
/ROW0: D1.1 (K), D2.1 (K), D3.1 (K), D4.1 (K), D5.1 (K), D6.1 (K), D7.1 (K), D8.1 (K), D9.1 (K), D10.1 (K), D11.1 (K), D12.1 (K), D13.1 (K), D14.1 (K), D72.1 (K), U1.2 (GPIO0)
/ROW1: D15.1 (K), D16.1 (K), D17.1 (K), D18.1 (K), D19.1 (K), D20.1 (K), D21.1 (K), D22.1 (K), D23.1 (K), D24.1 (K), D25.1 (K), D26.1 (K), D27.1 (K), D28.1 (K), D29.1 (K), U1.8 (GPIO6)
/ROW2: D30.1 (K), D31.1 (K), D32.1 (K), D33.1 (K), D34.1 (K), D35.1 (K), D36.1 (K), D37.1 (K), D38.1 (K), D39.1 (K), D40.1 (K), D41.1 (K), D42.1 (K), D43.1 (K), D44.1 (K), U1.7 (GPIO5)
/ROW3: D45.1 (K), D46.1 (K), D47.1 (K), D48.1 (K), D49.1 (K), D50.1 (K), D51.1 (K), D52.1 (K), D53.1 (K), D54.1 (K), D55.1 (K), D56.1 (K), D57.1 (K), D58.1 (K), U1.6 (GPIO4)
/ROW4: D59.1 (K), D60.1 (K), D61.1 (K), D62.1 (K), D63.1 (K), D64.1 (K), D65.1 (K), D66.1 (K), D67.1 (K), D68.1 (K), D69.1 (K), D70.1 (K), D71.1 (K), U1.5 (GPIO3)
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
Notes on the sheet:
USB-C · protection · 3.3 V supply
RP2040 · QSPI flash · crystal · boot/reset · decoupling
Key matrix · 82 × Kailh CPG151101S11 hot-swap sockets · 1N4148W · 6 rows × 16 columns · COL2ROW
CC1/CC2: 5.1 kΩ sink pull-downs. F1: 0.5 A hold-current PTC.
+3V3 decoupling
+1V1 decoupling
Hold BOOT while connecting USB (or press RESET while holding BOOT) to get the RPI-RP2 UF2 drive. A blank board enumerates as RPI-RP2 automatically. Test pads: RUN, +3V3, GND, +5V.
GPIO29
GPIO28
GPIO27
GPIO26
GPIO24
GPIO23
GPIO22
GPIO21
GPIO20
GPIO19
GPIO18
GPIO17
GPIO16
GPIO8
GPIO7
GPIO1
GPIO0
GPIO6
GPIO5
GPIO4
GPIO3
GPIO2
